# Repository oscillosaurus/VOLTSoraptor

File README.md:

# VOLTSoraptor
Adaptation of Mutable Instruments VOLTS for use as inline 5V regulator for a single Eurorack Module.

Original File from https://github.com/pichenettes/eurorack

You will need one of these - *OKI-78SR-5/1.5-W36H-C*

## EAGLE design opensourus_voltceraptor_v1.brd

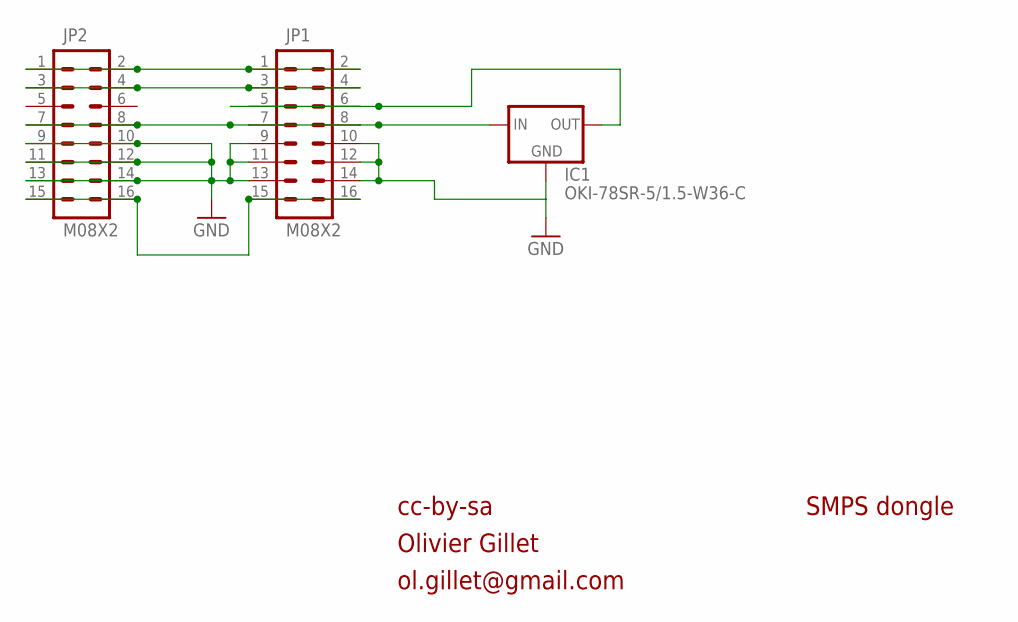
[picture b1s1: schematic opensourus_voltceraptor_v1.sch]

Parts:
IC1: OKI-78SR-5/1.5-W36-C; OKI78SR
JP1, JP2: M08X2; 2X8

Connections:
GND: IC1.2 (GND), JP1.9, JP1.10, JP1.11, JP1.12, JP1.13, JP1.14, JP2.9, JP2.10, JP2.11, JP2.12, JP2.13, JP2.14
unnamed: IC1.1 (IN), JP1.7, JP1.8, JP2.7, JP2.8
unnamed: IC1.3 (OUT), JP1.5, JP1.6
unnamed: JP1.15, JP1.16, JP2.15, JP2.16
unnamed: JP1.1, JP1.2, JP2.1, JP2.2
unnamed: JP1.3, JP1.4, JP2.3, JP2.4

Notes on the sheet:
cc-by-sa
Olivier Gillet
ol.gillet@gmail.com
SMPS dongle

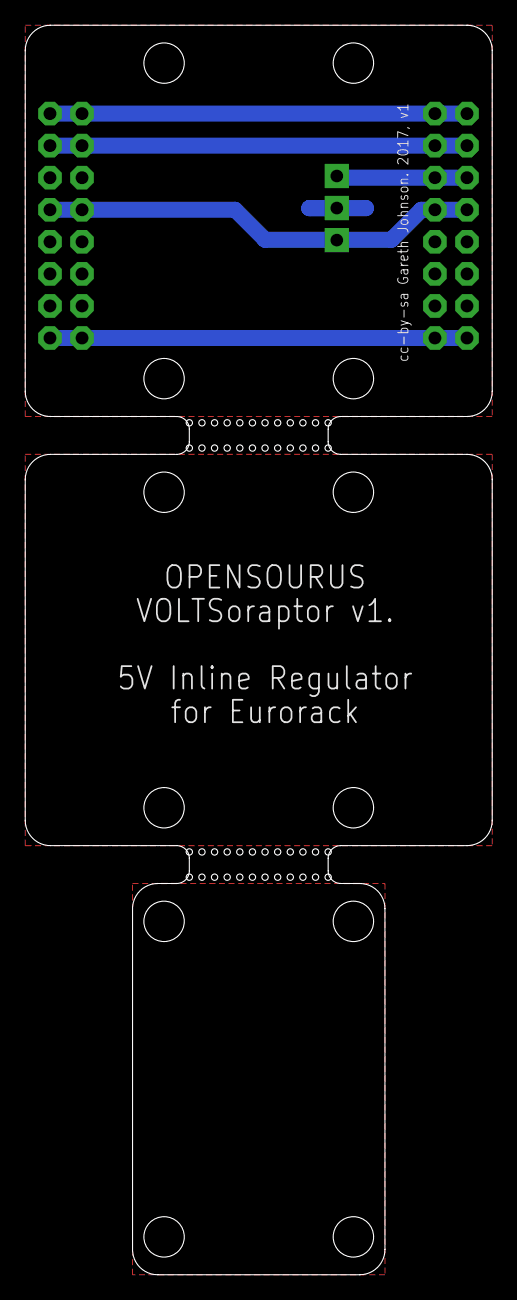
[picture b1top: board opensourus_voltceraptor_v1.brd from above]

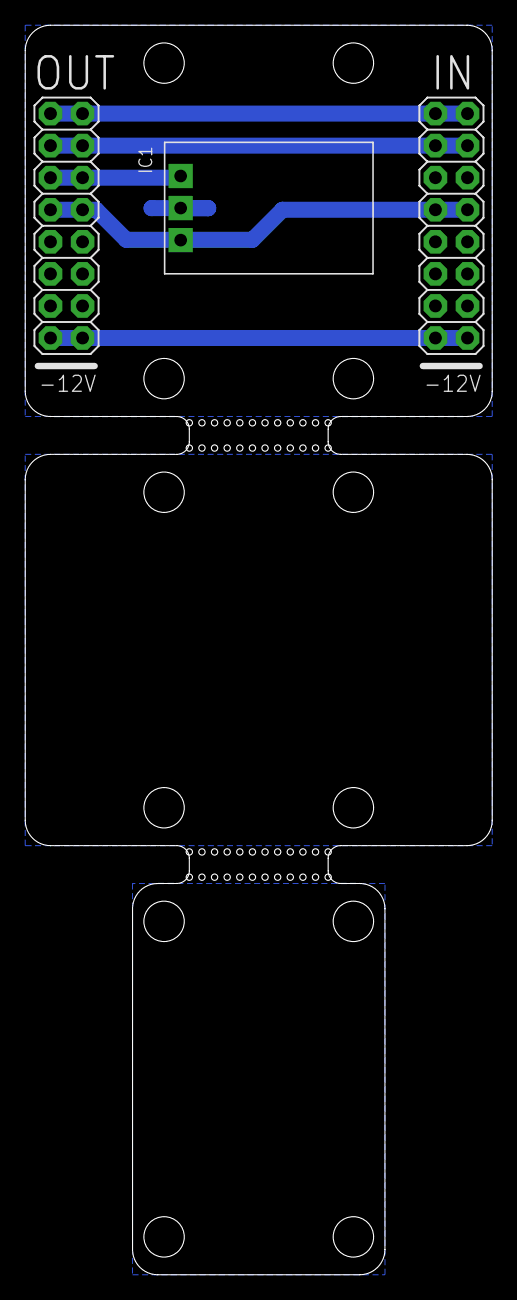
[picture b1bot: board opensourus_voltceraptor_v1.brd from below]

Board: 2 copper layers, 37.0 x 99.0 mm, 3 parts (3 on the bottom side), 6 nets.

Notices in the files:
opensourus_voltceraptor_v1.brd:
cc-by-sa Gareth Johnson. 2017, v1
